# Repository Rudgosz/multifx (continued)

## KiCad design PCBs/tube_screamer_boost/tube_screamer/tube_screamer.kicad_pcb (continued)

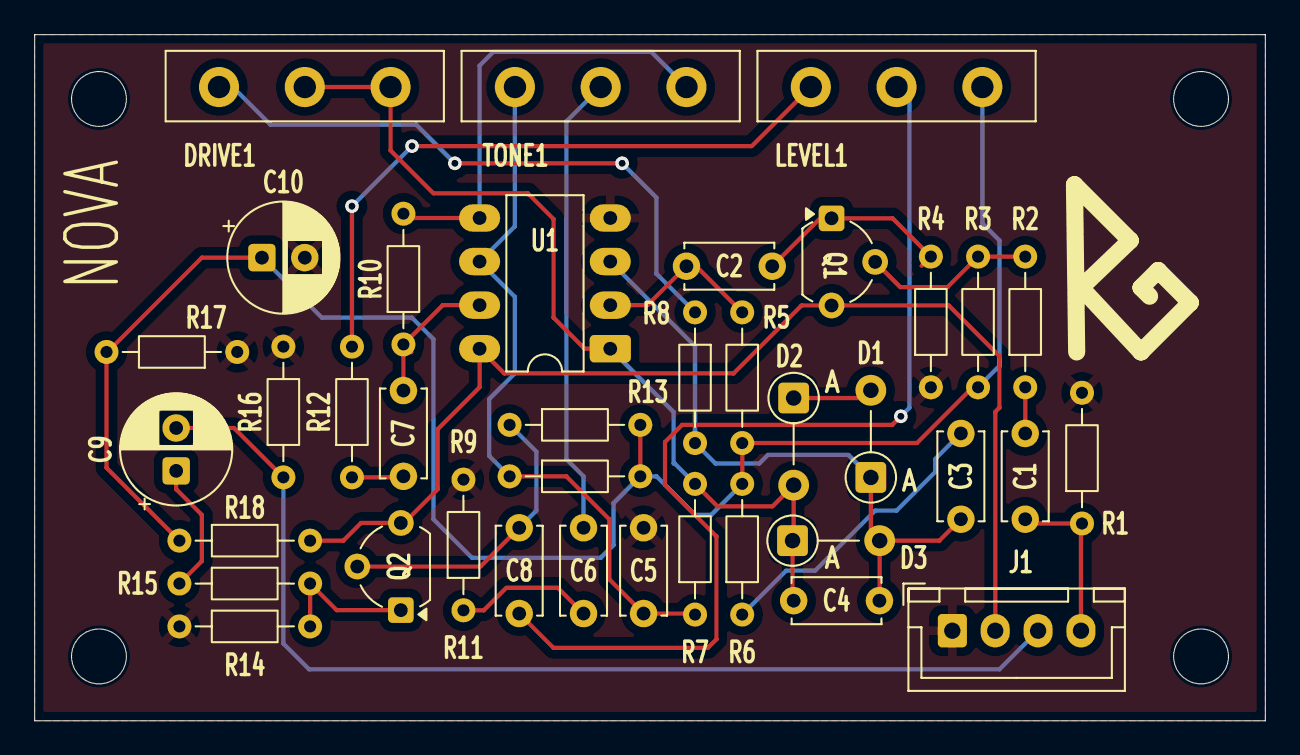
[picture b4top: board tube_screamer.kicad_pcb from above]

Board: 2 copper layers, 71.8 x 40.0 mm, 42 parts (0 on the bottom side), 25 nets.

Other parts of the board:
REF1, REF2, REF3, REF4: MountingHole_3.2mm_M3

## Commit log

2026-03-27 pcbs
